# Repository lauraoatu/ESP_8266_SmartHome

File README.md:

# ESP_8266_SmartHome
The system use many type of sensor such as : temperature, humidity, gas and other to generate graphics evolution into a web page.
# Open with Arduino IDE for code or Eagle AutoDesk for PCB and Schematic

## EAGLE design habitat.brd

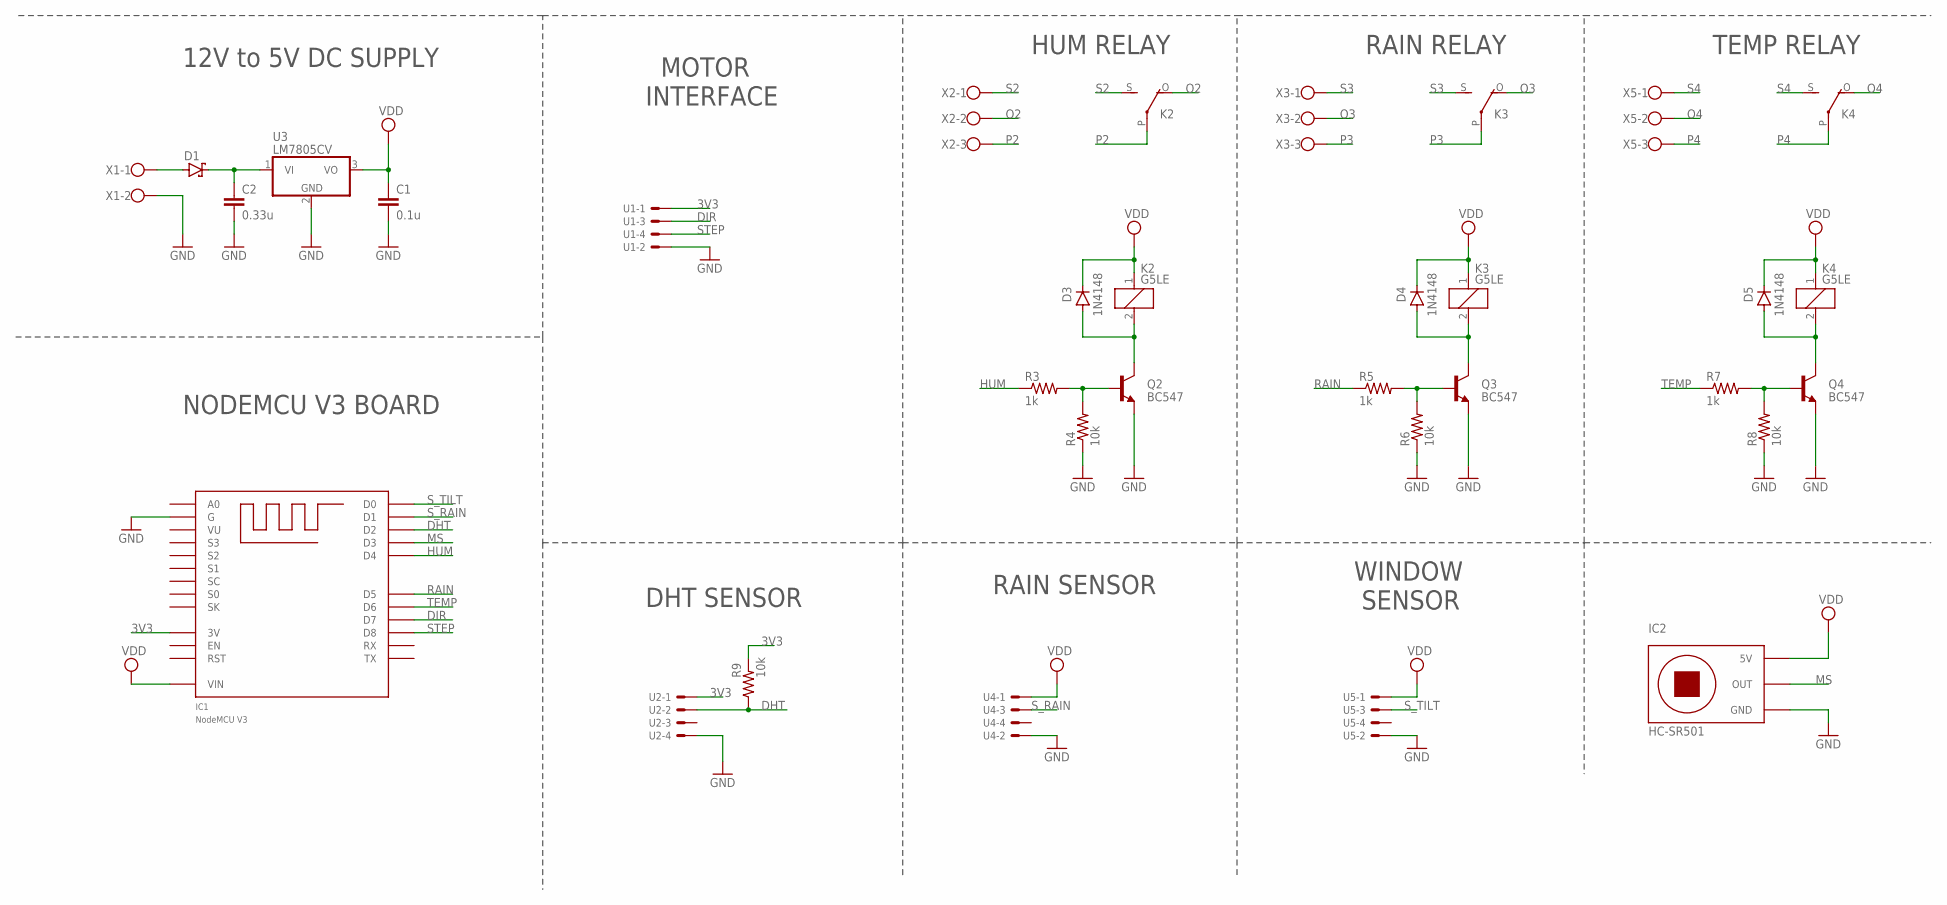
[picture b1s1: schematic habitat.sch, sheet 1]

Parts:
C1: 0.1u; C025-030X050
C2: 0.33u; C025-030X050
D1: 1N5817-T; DO41-7.6
D3, D4, D5: 1N4148; DO35-7
IC1: NODEMCU_V3
IC2: HC-SR501
K2, K3, K4: G5LE
Q2, Q3, Q4: BC547; TO92
R3, R5, R7: 1k; 0309/10
R4, R6, R8, R9: 10k; 0309/10
U1, U2, U4, U5: KK-156-4
U3: LM7805CV; TO220H
X1: W237-102
X2, X3, X5: W237-103

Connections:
3V3: IC1.P$11 (3V), IC1.P$16 (3V), IC1.P$25 (3V), R9.2, U1.1, U2.1
DHT: IC1.P$28 (D2), R9.1, U2.2
DIR: IC1.P$21 (D7), U1.3
GND: C1.2, C2.2, IC1.P$2 (G), IC1.P$10 (G), IC1.P$14 (G), IC1.P$17 (G), IC1.P$24 (G), IC2.GND, Q2.1 (E), Q3.1 (E), Q4.1 (E), R4.1, R6.1, R8.1, U1.2, U2.4, U3.2 (GND), U4.2, U5.2, X1.2
HUM: IC1.P$26 (D4), R3.1
MS: IC1.P$27 (D3), IC2.OUT
unnamed: C2.1, D1.C, U3.1 (VI)
unnamed: D1.A, X1.1
unnamed: D3.A, K2.2, Q2.3 (C)
unnamed: Q2.2 (B), R3.2, R4.2
unnamed: D4.A, K3.2, Q3.3 (C)
unnamed: Q3.2 (B), R5.2, R6.2
unnamed: D5.A, K4.2, Q4.3 (C)
unnamed: Q4.2 (B), R7.2, R8.2
O2: K2.O, X2.2
O3: K3.O, X3.2
O4: K4.O, X5.2
P2: K2.P, X2.3
P3: K3.P, X3.3
P4: K4.P, X5.3
RAIN: IC1.P$23 (D5), R5.1
S2: K2.S, X2.1
S3: K3.S, X3.1
S4: K4.S, X5.1
STEP: IC1.P$20 (D8), U1.4
S_RAIN: IC1.P$29 (D1), U4.3
S_TILT: IC1.P$30 (D0), U5.3
TEMP: IC1.P$22 (D6), R7.1
VDD: C1.1, D3.C, D4.C, D5.C, IC1.P$15 (VIN), IC2.VDD (5V), K2.1, K3.1, K4.1, U3.3 (VO), U4.1, U5.1

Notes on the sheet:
12V to 5V DC SUPPLY
NODEMCU V3 BOARD
DHT SENSOR
HUM RELAY
RAIN RELAY
TEMP RELAY
RAIN SENSOR
WINDOW SENSOR
MOTOR INTERFACE

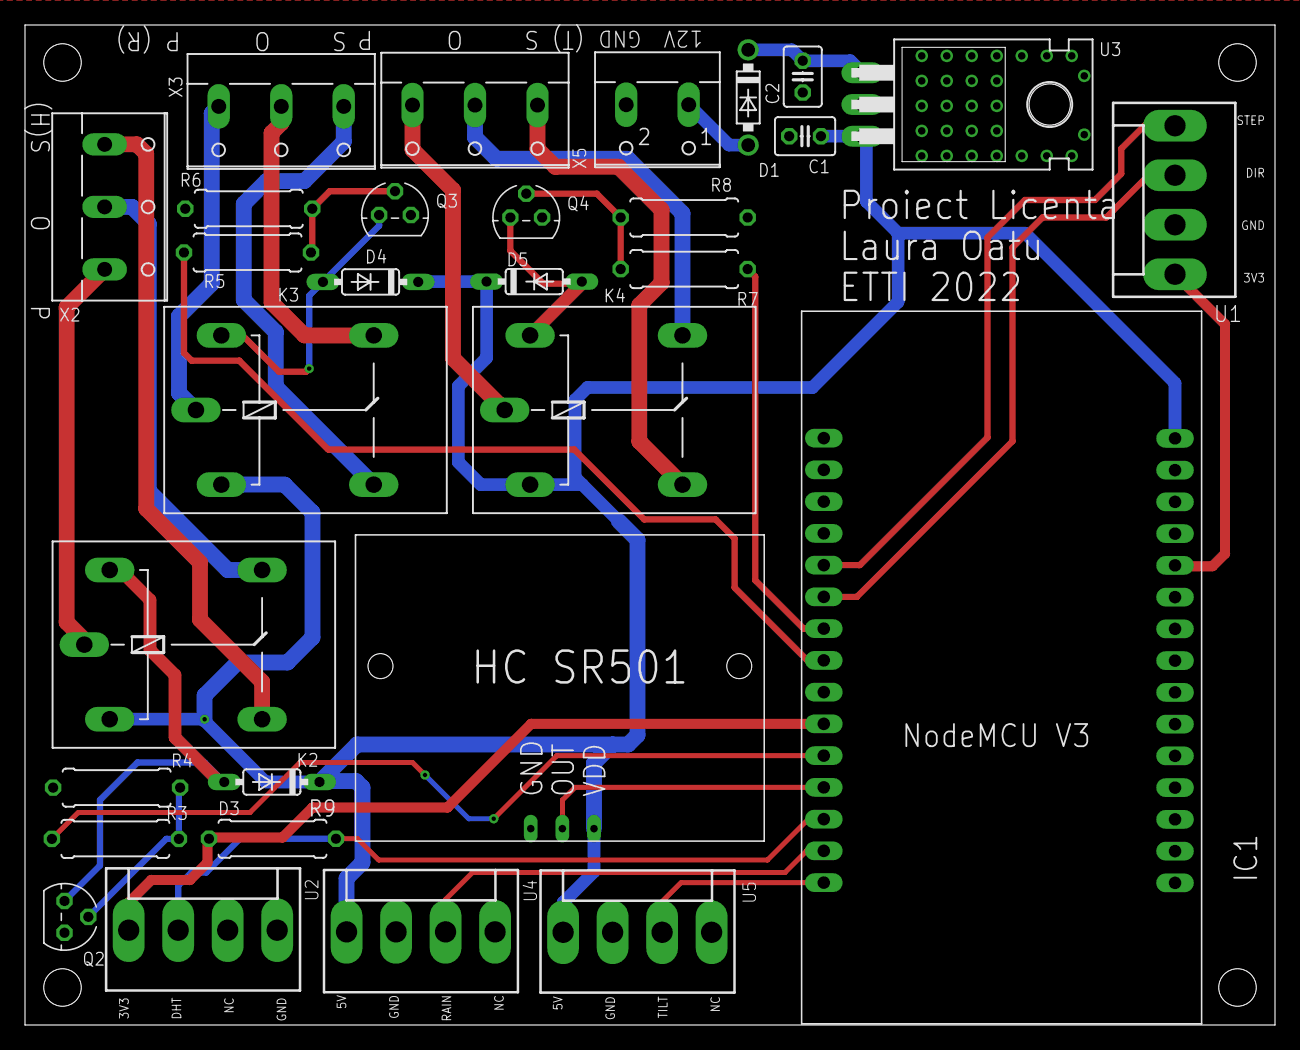
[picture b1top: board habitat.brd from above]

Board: 2 copper layers, 100.0 x 80.0 mm, 30 parts (0 on the bottom side), 29 nets.
